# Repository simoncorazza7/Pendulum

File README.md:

# Pendel

Cart-pole (inverted pendulum) rig: a stepper-driven cart on a rail, a pendulum on a quadrature encoder, and a
Raspberry Pi 4 on a custom carrier PCB running a 500 Hz C++ controller (`pendctl`). The controller runs either on
the Pi (local mode) or on a PC over UDP with a constant delay (remote mode).

## Documentation

- **New here? Start with [HANDOVER.md](HANDOVER.md):** where the project stands, the open problems, where everything
  is, and access.
- [Theory and technical reference](docs/01_theory_and_technical_reference.md): the rig, the physics and model,
  PID and cascade control, latency, hardware and pinout, software architecture, the remote protocol.
- [Setup and operation guide](docs/02_setup_and_operation_guide.md): installing git and Python, getting the code,
  reaching the Pi, running local and remote mode safely, changing settings, troubleshooting, cheat sheet.

Also: `CONTROL_BRIEF.md` (the project brief), `CLAUDE.md` (rules, conventions and current status), and the
design notes and measurements in `docs/`. [docs/README.md](docs/README.md) lists every document and says which are
current and which are dated records.

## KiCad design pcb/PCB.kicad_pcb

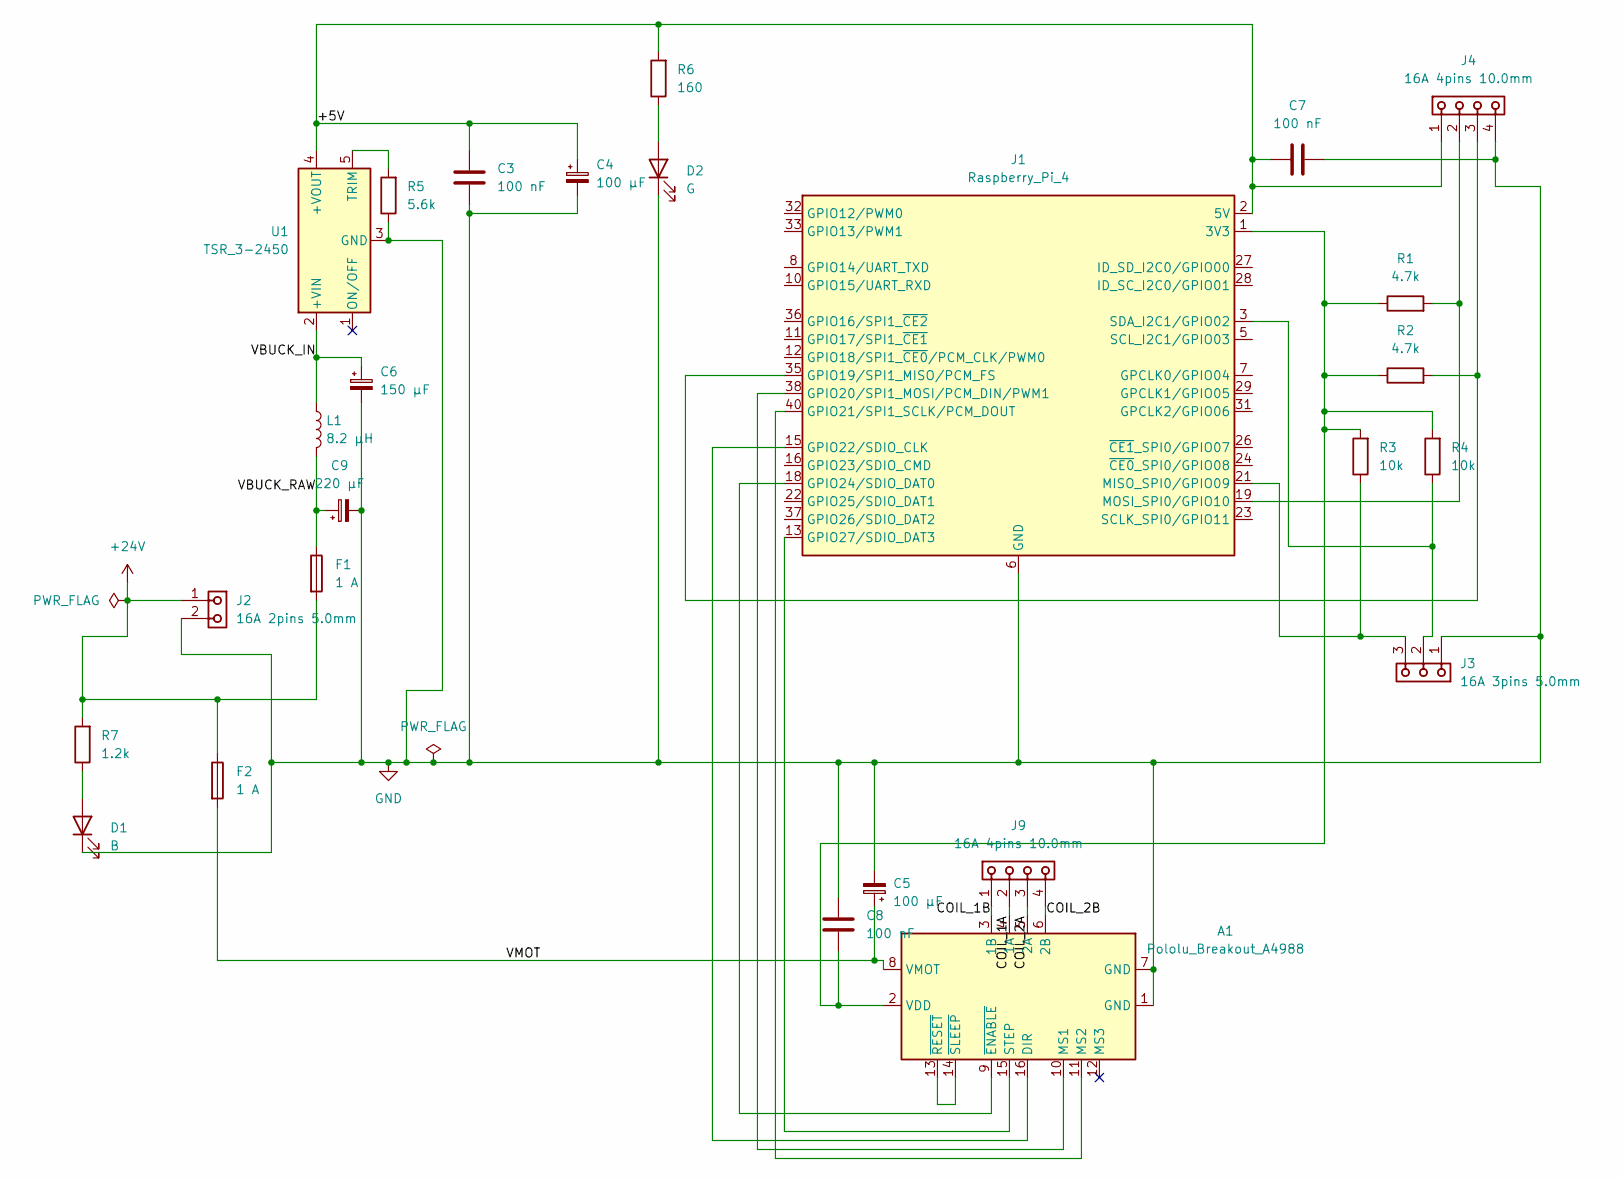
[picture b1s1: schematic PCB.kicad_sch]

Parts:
A1: Pololu_Breakout_A4988; Pololu_Breakout-16_15.2x20.3mm
C3, C7, C8: 100 nF; C_Disc_D5.1mm_W3.2mm_P5.00mm
C4, C5: 100 µF; CP_Radial_D10.0mm_P5.00mm
C6: 150 µF; CP_Radial_D10.0mm_P5.00mm
C9: 220 µF; CP_Radial_D10.0mm_P5.00mm
D1: B; LED_D3.0mm
D2: G; LED_D3.0mm
F1, F2: 1 A; Fuseholder_Cylinder-5x20mm_Schurter_0031_8201_Horizontal_Op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
J1: Raspberry_Pi_4; Raspberry_Pi_4_Socketed_THT_FaceDown_MountingHoles
J2: 691101710002; J_Wurth_WR-TBL_691317410002; Part Number 691101710002
J3: 691101710003; J_Wurth_WR-TBL_691317410003; Part Number 691101710003
J4, J9: 691101810004; J_Wurth_WR-TBL_691317410004; Part Number 691101810004
L1: 8.2 µH; L_0805_2012Metric_Pad1.05x1.20mm_HandSolder
R1, R2: 4.7k; R_Axial_DIN0207_L6.3mm_D2.5mm_P10.16mm_Horizontal
R3, R4: 10k; R_Axial_DIN0207_L6.3mm_D2.5mm_P10.16mm_Horizontal
R5: 5.6k; R_Axial_DIN0207_L6.3mm_D2.5mm_P10.16mm_Horizontal
R6: 160; R_Axial_DIN0207_L6.3mm_D2.5mm_P10.16mm_Horizontal
R7: 1.2k; R_Axial_DIN0207_L6.3mm_D2.5mm_P10.16mm_Horizontal
U1: TSR_3-2450; Converter_DCDC_TRACO_TSR-3-24xx_SIP5_THT

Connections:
+24V: F1.2, F2.1, J2.1, R7.2
/+5V: C3.1, C4.1, C7.1, J1.2 (5V), J1.4 (5V), J4.1, R6.2, U1.4 (+VOUT)
/COIL_1A: A1.4 (1A), J9.2
/COIL_1B: A1.3 (1B), J9.1
/COIL_2A: A1.5 (2A), J9.3
/COIL_2B: A1.6 (2B), J9.4
/VBUCK_IN: C6.1, L1.1, U1.2 (+VIN)
/VBUCK_RAW: C9.1, F1.1, L1.2
/VMOT: A1.8 (VMOT), C5.1, F2.2
GND: A1.1 (GND), A1.7 (GND), C3.2, C4.2, C5.2, C6.2, C7.2, C8.1, C9.2, D1.1 (K), D2.1 (K), J1.6 (GND), J1.9 (GND), J1.14 (GND), J1.20 (GND), J1.25 (GND), J1.30 (GND), J1.34 (GND), J1.39 (GND), J2.2, J3.1, J4.4, R5.1, U1.3 (GND)
unnamed: A1.16 (DIR), J1.15 (GPIO22/SDIO_CLK)
unnamed: A1.10 (MS1), J1.38 (GPIO20/SPI1_MOSI/PCM_DIN/PWM1)
unnamed: A1.11 (MS2), J1.40 (GPIO21/SPI1_SCLK/PCM_DOUT)
unnamed: A1.15 (STEP), J1.13 (GPIO27/SDIO_DAT3)
unnamed: A1.2 (VDD), C8.2, J1.1 (3V3), J1.17 (3V3), R1.1, R2.1, R3.2, R4.2
unnamed: A1.9 (~ENABLE), J1.18 (GPIO24/SDIO_DAT0)
unnamed: A1.13 (~RESET), A1.14 (~SLEEP)
unnamed: D1.2 (A), R7.1
unnamed: D2.2 (A), R6.1
unnamed: J1.35 (GPIO19/SPI1_MISO/PCM_FS), J4.3, R2.2
unnamed: J1.21 (MISO_SPI0/GPIO09), J3.3, R3.1
unnamed: J1.19 (MOSI_SPI0/GPIO10), J4.2, R1.2
unnamed: J1.3 (SDA_I2C1/GPIO02), J3.2, R4.1
unnamed: R5.2, U1.5 (TRIM)

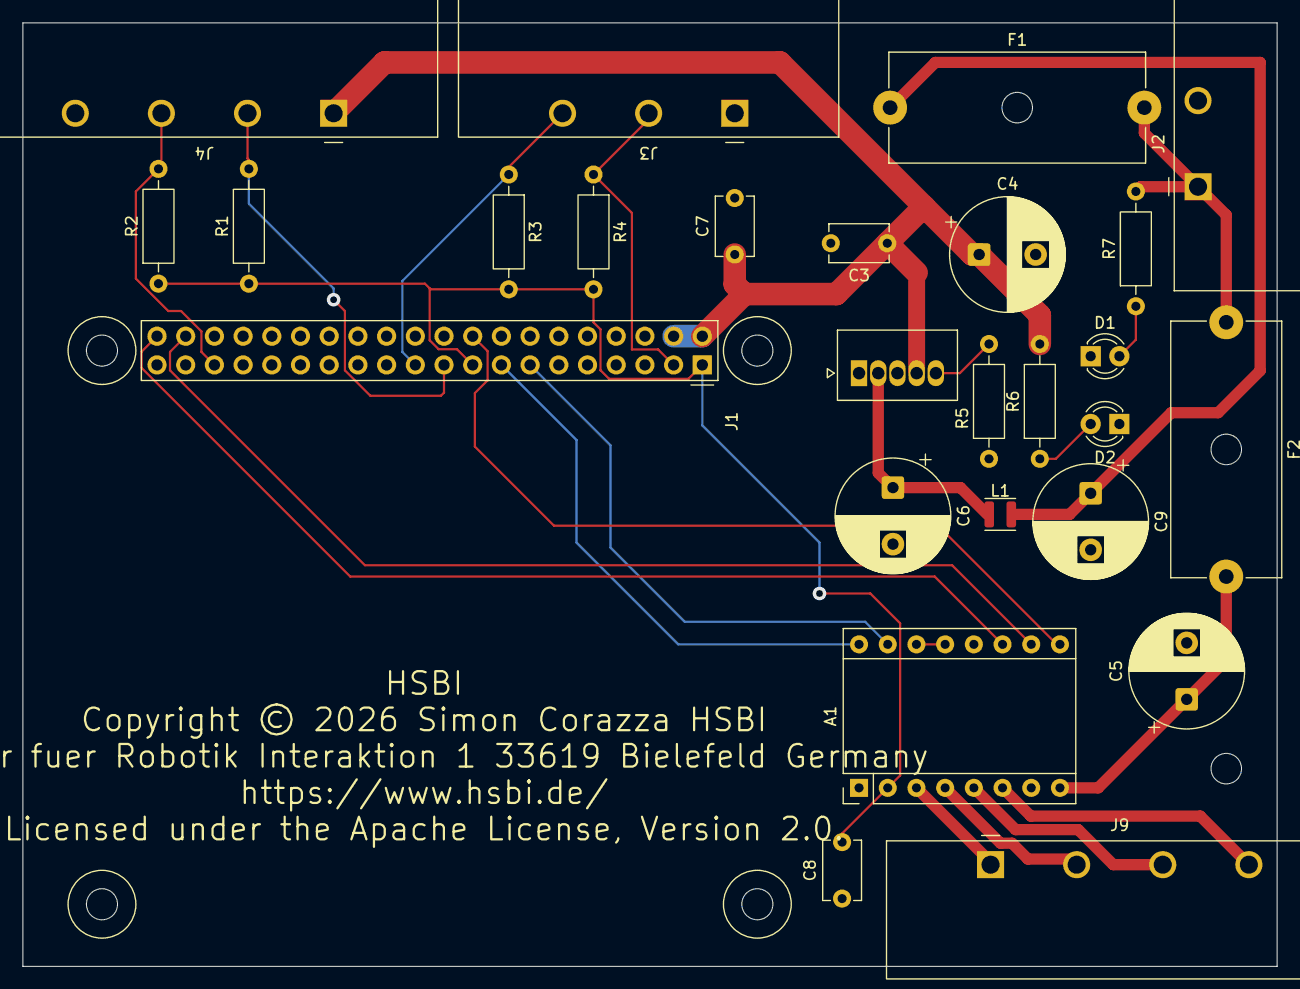
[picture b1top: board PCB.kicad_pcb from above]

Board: 2 copper layers, 111.0 x 83.5 mm, 26 parts (0 on the bottom side), 24 nets.

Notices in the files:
pcb/PCB.kicad_pcb:
Copyright © 2026 Simon Corazza HSBI
Licensed under the Apache License, Version 2.0.
